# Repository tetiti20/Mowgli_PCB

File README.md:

# Mowgli_PCB
PI-HAT for mower OpenMower Mowgli project

https://github.com/Mowglifrenchtouch  
https://github.com/juditech3D/Guide-DIY-OpenMower-Mowgli-pour-Robots-Tondeuses-Yard500-et-500B

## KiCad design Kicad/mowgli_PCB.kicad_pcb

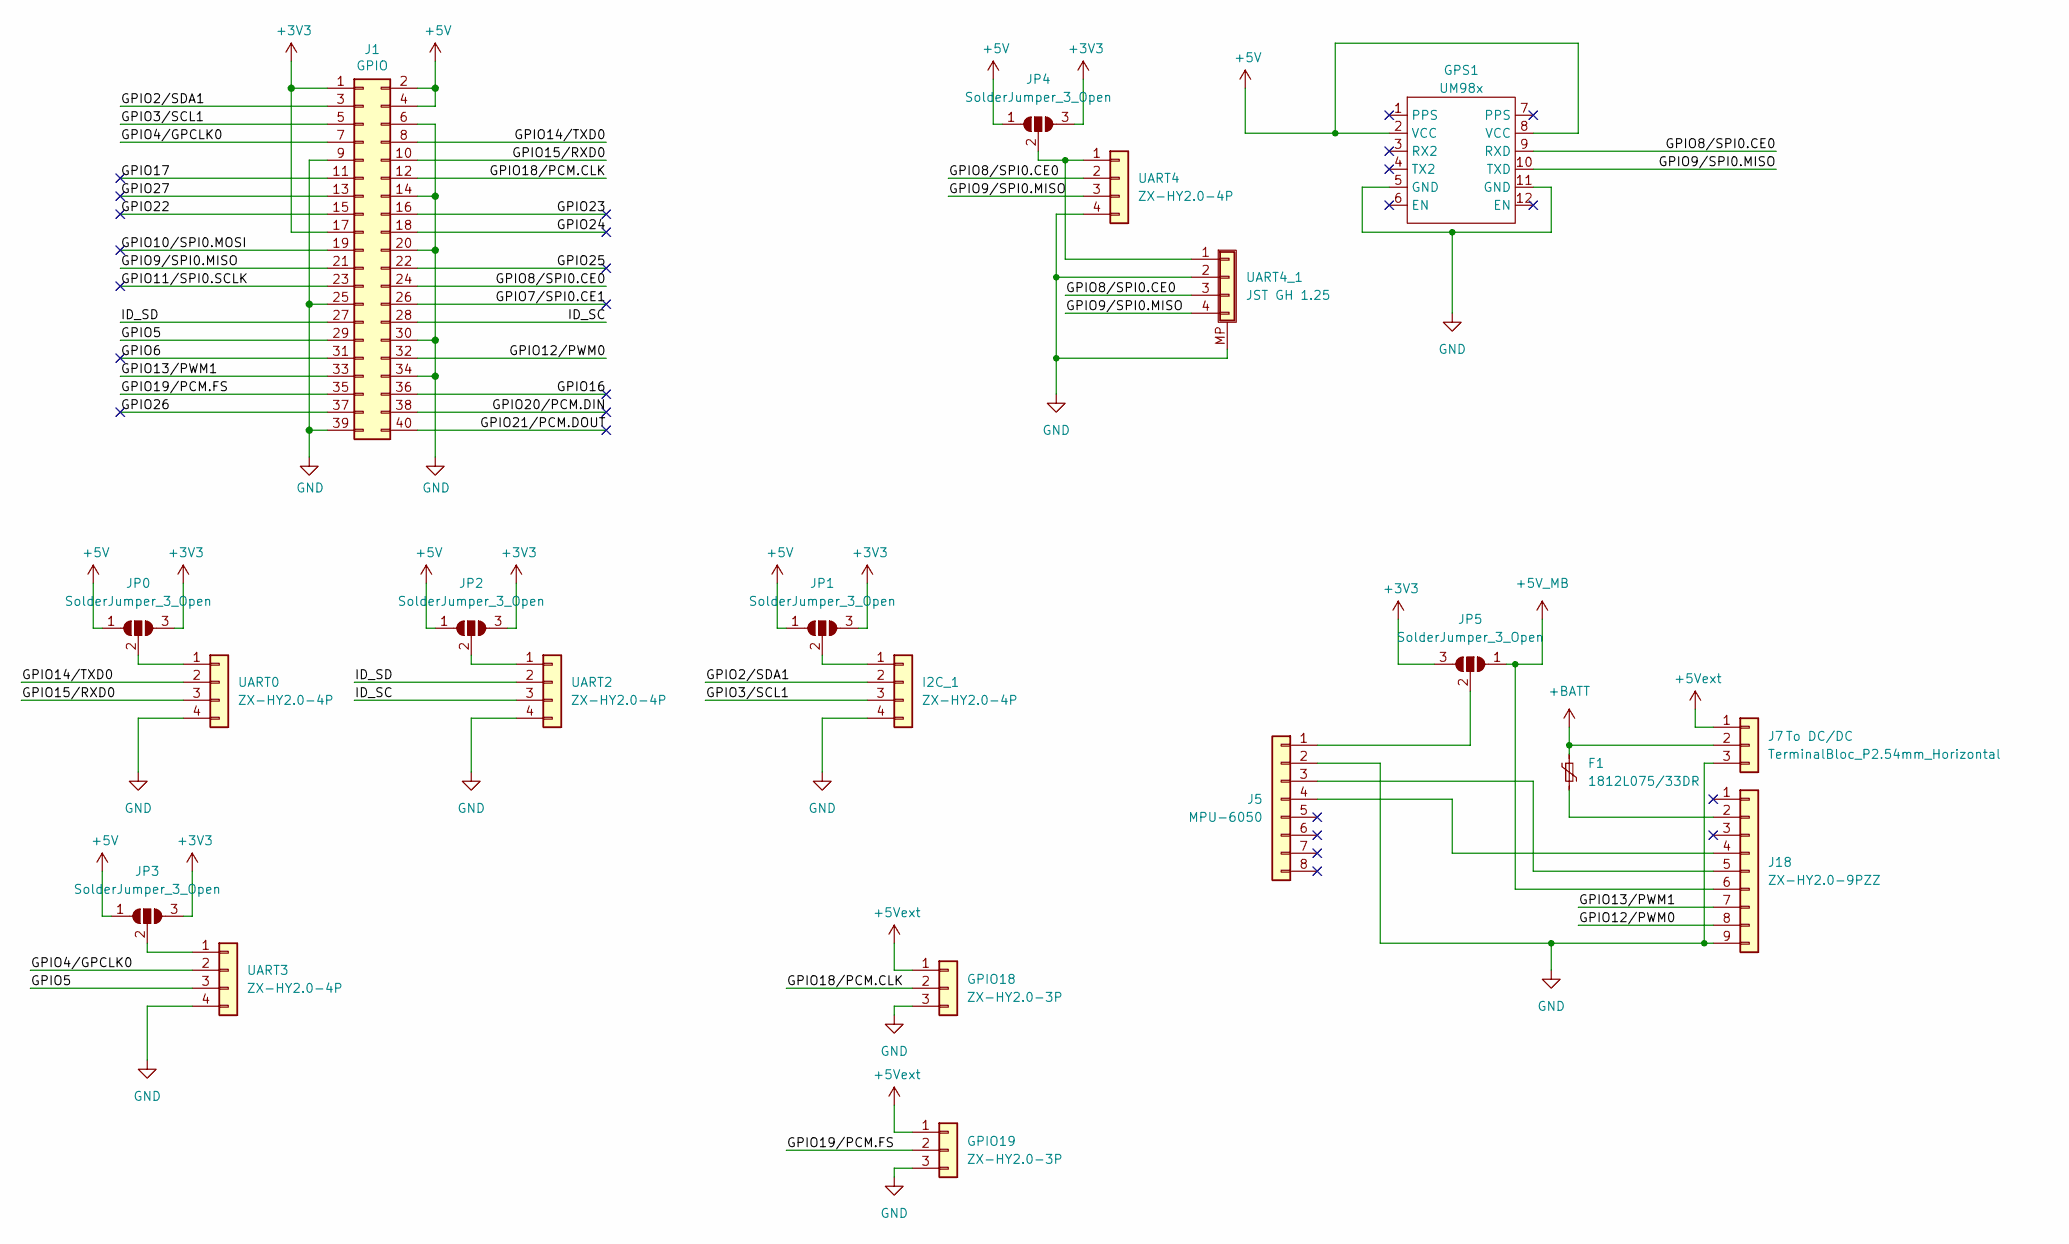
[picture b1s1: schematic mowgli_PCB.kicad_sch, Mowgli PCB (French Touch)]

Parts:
F1: 1812L075/33DR; Fuse_1812_4532Metric
GPIO18, GPIO19: ZX-HY2.0-3P; Connector_JST_HY2.0_1x03_P2.00mm_THT
GPS1: UM98x; UM9XX_WitMotion
I2C_1: ZX-HY2.0-4P; Connector_JST_HY2.0_1x04_P2.00mm_THT_1
J1: GPIO; PinSocket_2x20_P2.54mm_Vertical
J5: MPU-6050; GY-521
J7: TerminalBloc_P2.54mm_Horizontal; TerminalBlock_Phoenix_MPT-0,5-3-2.54_1x03_P2.54mm_Horizontal
J18: ZX-HY2.0-9PZZ; Connector_JST_HY2.0_1x09_P2.00mm_THT_1_1
JP0, JP1, JP2, JP3, JP4, JP5: SolderJumper_3_Open; SolderJumper-3_P1.3mm_Open_RoundedPad1.0x1.5mm
UART0, UART2, UART3, UART4: ZX-HY2.0-4P; Connector_JST_HY2.0_1x04_P2.00mm_THT_1
UART4_1: JST GH 1.25; JST_GH_SM04B-GHS-TB_1x04-1MP_P1.25mm_Horizontal

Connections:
+3V3: J1.1, J1.17, JP0.3 (B), JP1.3 (B), JP2.3 (B), JP3.3 (B), JP4.3 (B), JP5.3 (B)
+5V: GPS1.2 (VCC), GPS1.8 (VCC), J1.2, J1.4, JP0.1 (A), JP1.1 (A), JP2.1 (A), JP3.1 (A), JP4.1 (A)
+5V_MB: J18.6, JP5.1 (A)
+5Vext: GPIO18.1, GPIO19.1, J7.1
+BATT: F1.1, J7.2
/GPIO2/SDA1: I2C_1.2, J1.3
/GPIO3/SCL1: I2C_1.3, J1.5
/GPIO4/GPCLK0: J1.7, UART3.2
/GPIO5: J1.29, UART3.3
/GPIO6: J1.31
/GPIO7/SPI0.CE1: J1.26
/GPIO8/SPI0.CE0: GPS1.9 (RXD), J1.24, UART4.2, UART4_1.3
/GPIO9/SPI0.MISO: GPS1.10 (TXD), J1.21, UART4.3, UART4_1.4
/GPIO10/SPI0.MOSI: J1.19
/GPIO11/SPI0.SCLK: J1.23
/GPIO12/PWM0: J1.32, J18.8
/GPIO13/PWM1: J1.33, J18.7
/GPIO14/TXD0: J1.8, UART0.2
/GPIO15/RXD0: J1.10, UART0.3
/GPIO16: J1.36
/GPIO17: J1.11
/GPIO18/PCM.CLK: GPIO18.2, J1.12
/GPIO19/PCM.FS: GPIO19.2, J1.35
/GPIO20/PCM.DIN: J1.38
/GPIO21/PCM.DOUT: J1.40
/GPIO22: J1.15
/GPIO23: J1.16
/GPIO24: J1.18
/GPIO25: J1.22
/GPIO26: J1.37
/GPIO27: J1.13
/ID_SC: J1.28, UART2.3
/ID_SD: J1.27, UART2.2
GND: GPIO18.3, GPIO19.3, GPS1.5 (GND), GPS1.11 (GND), I2C_1.4, J1.6, J1.9, J1.14, J1.20, J1.25, J1.30, J1.34, J1.39, J5.2, J7.3, J18.9, UART0.4, UART2.4, UART3.4, UART4.4, UART4_1.2, UART4_1.MP (Shield)
unnamed: I2C_1.1, JP1.2 (C)
unnamed: J5.1, JP5.2 (C)
unnamed: F1.2, J18.2
unnamed: J5.4, J18.4
unnamed: J5.3, J18.5
unnamed: JP0.2 (C), UART0.1
unnamed: JP2.2 (C), UART2.1
unnamed: JP3.2 (C), UART3.1
unnamed: JP4.2 (C), UART4.1, UART4_1.1

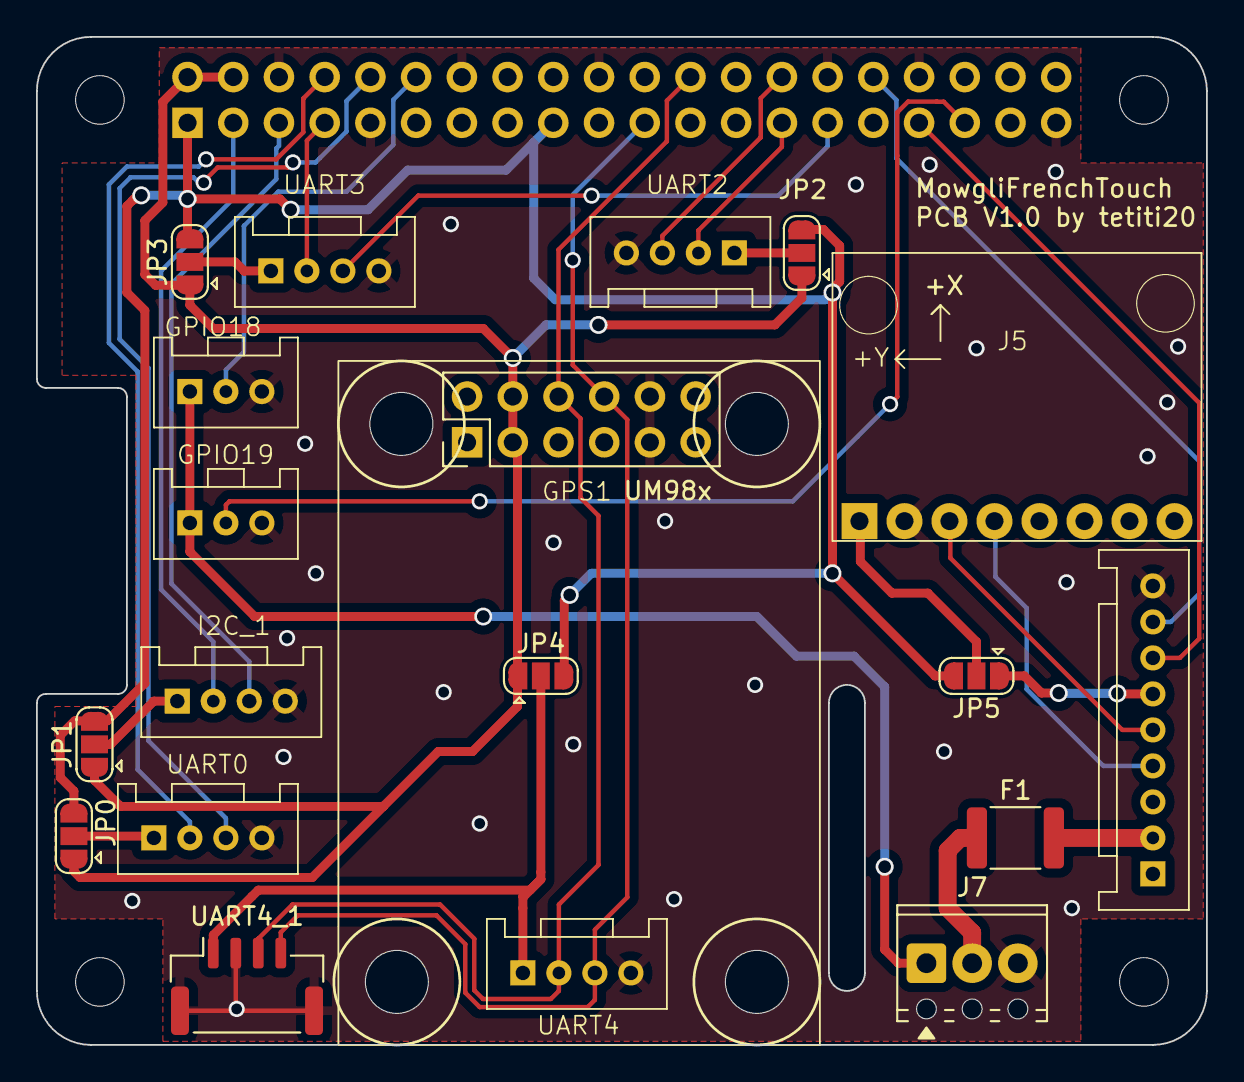
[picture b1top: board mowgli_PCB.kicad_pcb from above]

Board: 2 copper layers, 65.0 x 56.0 mm, 24 parts (1 on the bottom side), 29 nets.

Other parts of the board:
MH1, MH2, MH3, MH4: MountingHole_2.7mm_M2.5

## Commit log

2025-05-12 First version
2025-05-22 Correction inversion des pin 4 et 6 de J18
2025-05-22 Maj plan de masse après modif J18
2025-09-04 Create Photos
2025-09-04 Create test
